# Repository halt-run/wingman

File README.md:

# wingman
A secondary macropad that attaches to your regular TKL and provides the extra keys you need for all your late night gaming sessions.

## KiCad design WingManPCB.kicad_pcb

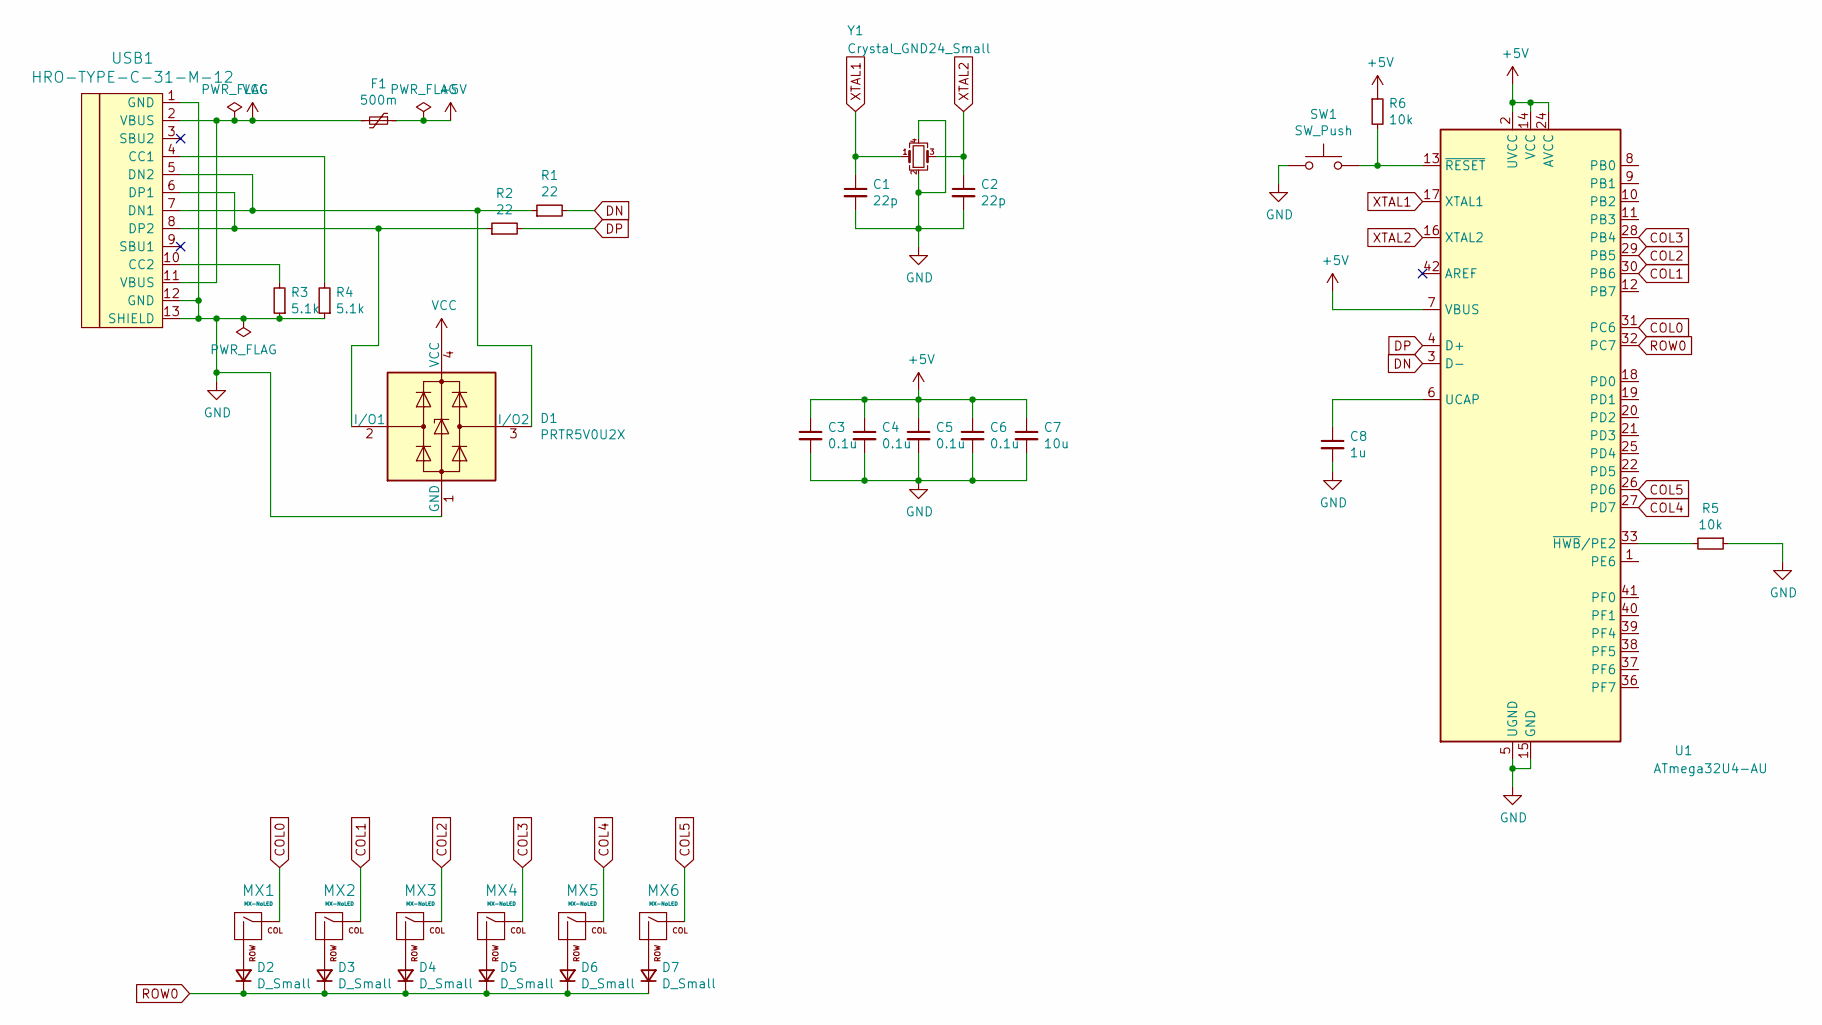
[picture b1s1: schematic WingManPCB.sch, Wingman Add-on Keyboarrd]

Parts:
C1, C2: 22p; C_0805_2012Metric
C3, C4, C5, C6: 0.1u; C_0805_2012Metric
C7: 10u; C_0805_2012Metric
C8: 1u; C_0805_2012Metric
D1: PRTR5V0U2X; SOT-143
D2, D3, D4, D5, D6, D7: D_Small; D_SOD-123
F1: 500m; Fuse_1206_3216Metric
MX1, MX2, MX3, MX4, MX5, MX6: MX-NoLED; MXOnly-1U-NoLED
R1, R2: 22; R_0805_2012Metric
R3, R4: 5.1k; R_0805_2012Metric
R5, R6: 10k; R_0805_2012Metric
SW1: SW_Push; SW_SPST_SKQG_WithStem
U1: ATmega32U4-AU; TQFP-44_10x10mm_P0.8mm
USB1: HRO-TYPE-C-31-M-12; HRO-TYPE-C-31-M-12-Assembly
Y1: Crystal_GND24_Small; Crystal_SMD_3225-4Pin_3.2x2.5mm

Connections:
+5V: C3.1, C4.1, C5.1, C6.1, C7.1, F1.1, R6.1, U1.2 (UVCC), U1.7 (VBUS), U1.14 (VCC), U1.24 (AVCC), U1.34 (VCC), U1.44 (AVCC)
COL0: MX1.1 (COL), U1.31 (PC6)
COL1: MX2.1 (COL), U1.30 (PB6)
COL2: MX3.1 (COL), U1.29 (PB5)
COL3: MX4.1 (COL), U1.28 (PB4)
COL4: MX5.1 (COL), U1.27 (PD7)
COL5: MX6.1 (COL), U1.26 (PD6)
DN: R1.2, U1.3 (D-)
DP: R2.2, U1.4 (D+)
GND: C1.2, C2.2, C3.2, C4.2, C5.2, C6.2, C7.2, C8.2, D1.1 (GND), R3.1, R4.1, R5.1, SW1.1, U1.5 (UGND), U1.15 (GND), U1.23 (GND), U1.35 (GND), U1.43 (GND), USB1.1 (GND), USB1.12 (GND), USB1.13 (SHIELD), Y1.2, Y1.4
unnamed: C8.1, U1.6 (UCAP)
unnamed: D1.2 (I/O1), R2.1, USB1.6 (DP1), USB1.8 (DP2)
unnamed: D1.3 (I/O2), R1.1, USB1.5 (DN2), USB1.7 (DN1)
unnamed: D2.2 (A), MX1.2 (ROW)
unnamed: D3.2 (A), MX2.2 (ROW)
unnamed: D4.2 (A), MX3.2 (ROW)
unnamed: D5.2 (A), MX4.2 (ROW)
unnamed: D6.2 (A), MX5.2 (ROW)
unnamed: D7.2 (A), MX6.2 (ROW)
unnamed: R3.2, USB1.10 (CC2)
unnamed: R4.2, USB1.4 (CC1)
unnamed: R5.2, U1.33 (~HWB~/PE2)
unnamed: R6.2, SW1.2, U1.13 (~RESET)
ROW0: D2.1 (K), D3.1 (K), D4.1 (K), D5.1 (K), D6.1 (K), D7.1 (K), U1.32 (PC7)
VCC: D1.4 (VCC), F1.2, USB1.2 (VBUS), USB1.11 (VBUS)
XTAL1: C1.1, U1.17 (XTAL1), Y1.1
XTAL2: C2.1, U1.16 (XTAL2), Y1.3

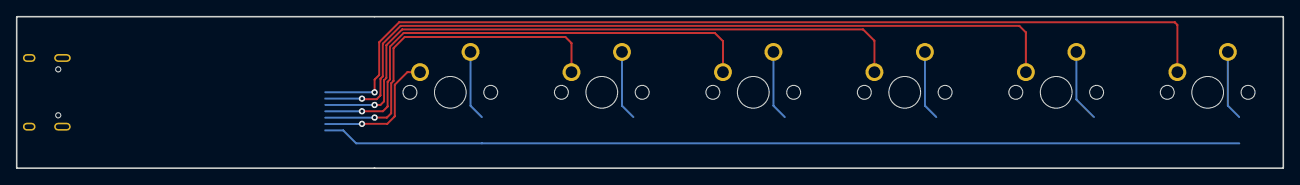
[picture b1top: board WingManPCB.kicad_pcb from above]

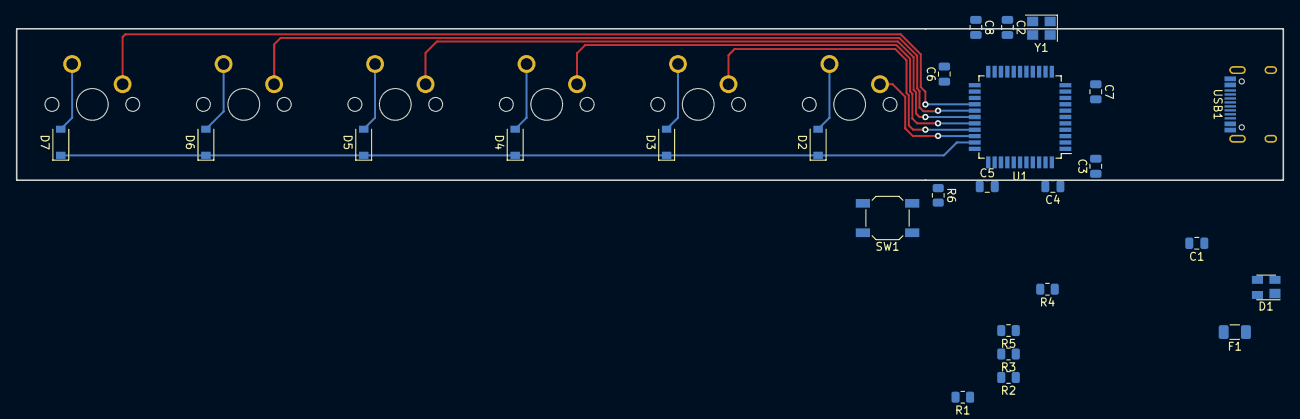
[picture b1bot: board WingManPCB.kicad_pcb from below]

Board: 2 copper layers, 159.3 x 19.1 mm, 32 parts (26 on the bottom side), 27 nets.

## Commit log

2021-04-16 KiCad Project added
2021-04-16 Resetting PCB project files
2021-04-16 KiCad Project Initialized
2021-04-16 Added ai03 Submodules
2021-04-16 Schematic begun
2021-04-16 Beginning the schematic work
2021-04-17 Schematic complete
2021-04-17 Sch complete, matrix routed, components mostly placed
2021-04-17 PCB Outline Added
